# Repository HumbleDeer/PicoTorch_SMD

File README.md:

# PicoTorch

Forked from [kdb424]/[PicoTorch] under the [Fork Off Public License].

WIP heater and fan board. Specs will come later after a release version is finalized.
Fork is here to try and add SMD compatibility without compromising on the original design or THT parts.

[kdb424]: https://git.kdb424.xyz/kdb424
[PicoTorch]: https://git.kdb424.xyz/kdb424/PicoTorch 
[Fork Off Public License]: https://github.com/klardotsh/fork-off-public-license

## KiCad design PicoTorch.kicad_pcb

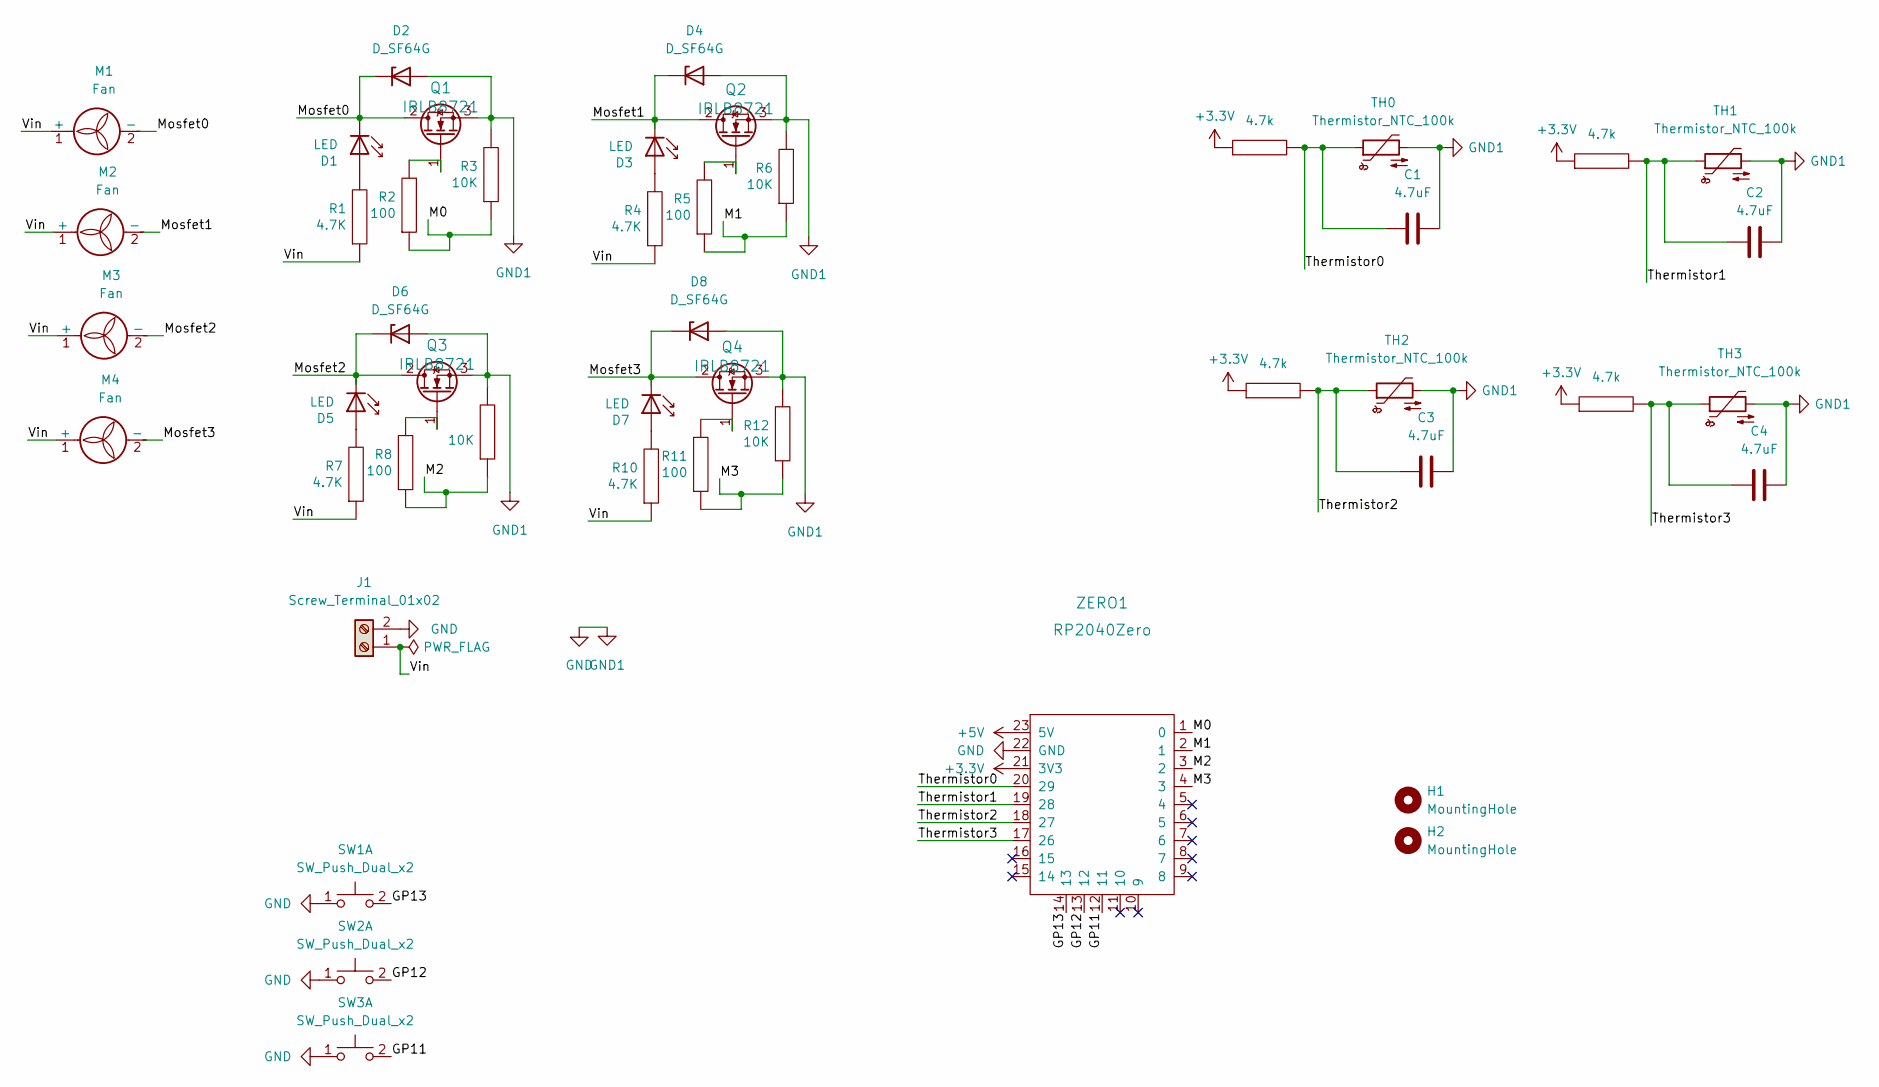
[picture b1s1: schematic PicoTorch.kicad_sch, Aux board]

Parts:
C1, C2, C3, C4: 4.7uF; CP_Radial_D4.0mm_P1.50mm
D1, D3, D5, D7: LED; LED_D1.8mm_W3.3mm_H2.4mm
D2, D4, D6, D8: D_SF64G; D_DO-34_SOD68_P7.62mm_Horizontal
H1, H2: MountingHole; MountingHole_3.2mm_M3_DIN965_Pad
J1: Screw_Terminal_01x02; TerminalBlock_Phoenix_MKDS-1,5-2_1x02_P5.00mm_Horizontal
M1, M2, M3: Fan; JST_XH_B2B-XH-A_1x02_P2.50mm_Vertical
M4: Fan; TerminalBlock_Phoenix_MKDS-1,5-2_1x02_P5.00mm_Horizontal
Q1, Q2, Q3, Q4: IRLB8721; TO-220-3_Horizontal_TabDown; MPN IRLML6344TRPBF; Digi-Key_PN IRLML6344TRPBFCT-ND
R1, R4, R7, R10: 4.7K; R_Axial_DIN0207_L6.3mm_D2.5mm_P2.54mm_Vertical; MPN RC0805JR-074K7L; LCSC C17673
R2, R5, R8, R11: 100; R_Axial_DIN0207_L6.3mm_D2.5mm_P2.54mm_Vertical; MPN RC0805JR-07100RL; LCSC C17408
R3, R6, R9, R12: 10K; R_Axial_DIN0207_L6.3mm_D2.5mm_P2.54mm_Vertical; MPN RC0805JR-0710KL; LCSC C17414
SW1, SW2, SW3: SW_Push_Dual_x2; JST_XH_B2B-XH-A_1x02_P2.50mm_Vertical
T1R1, T1R2, T1R3, T1R4: 4.7k; R_Axial_DIN0207_L6.3mm_D2.5mm_P2.54mm_Vertical
TH0, TH1, TH2, TH3: Thermistor_NTC_100k; JST_XH_B2B-XH-A_1x02_P2.50mm_Vertical
ZERO1: RP2040Zero; rp2040-zero-tht

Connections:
+3.3V: T1R1.1, T1R2.1, T1R3.1, T1R4.1, ZERO1.21 (3V3)
+5V: ZERO1.23 (5V)
/GP11: SW3.2 (D), ZERO1.12 (11)
/GP12: SW2.2 (D), ZERO1.13 (12)
/GP13: SW1.2 (D), ZERO1.14 (13)
/M0: R2.1, R3.1, ZERO1.1 (0)
/M1: R5.1, R6.1, ZERO1.2 (1)
/M2: R8.1, R9.1, ZERO1.3 (2)
/M3: R11.1, R12.1, ZERO1.4 (3)
/Mosfet0: D1.1 (K), D2.1 (K), M1.2 (-), Q1.2 (D)
/Mosfet1: D3.1 (K), D4.1 (K), M2.2 (-), Q2.2 (D)
/Mosfet2: D5.1 (K), D6.1 (K), M3.2 (-), Q3.2 (D)
/Mosfet3: D7.1 (K), D8.1 (K), M4.2 (-), Q4.2 (D)
/Thermistor0: C1.1, T1R1.2, TH0.1, ZERO1.20 (29)
/Thermistor1: C2.1, T1R2.2, TH1.1, ZERO1.19 (28)
/Thermistor2: C3.1, T1R3.2, TH2.1, ZERO1.18 (27)
/Thermistor3: C4.1, T1R4.2, TH3.1, ZERO1.17 (26)
/Vin: J1.1, M1.1 (+), M2.1 (+), M3.1 (+), M4.1 (+), R1.1, R4.1, R7.1, R10.1
GND: C1.2, C2.2, C3.2, C4.2, D2.2 (A), D4.2 (A), D6.2 (A), D8.2 (A), J1.2, Q1.3 (S), Q2.3 (S), Q3.3 (S), Q4.3 (S), R3.2, R6.2, R9.2, R12.2, SW1.1 (C), SW2.1 (C), SW3.1 (C), TH0.2, TH1.2, TH2.2, TH3.2, ZERO1.22 (GND)
unnamed: D1.2 (A), R1.2
unnamed: D3.2 (A), R4.2
unnamed: D5.2 (A), R7.2
unnamed: D7.2 (A), R10.2
unnamed: Q1.1 (G), R2.2
unnamed: Q2.1 (G), R5.2
unnamed: Q3.1 (G), R8.2
unnamed: Q4.1 (G), R11.2

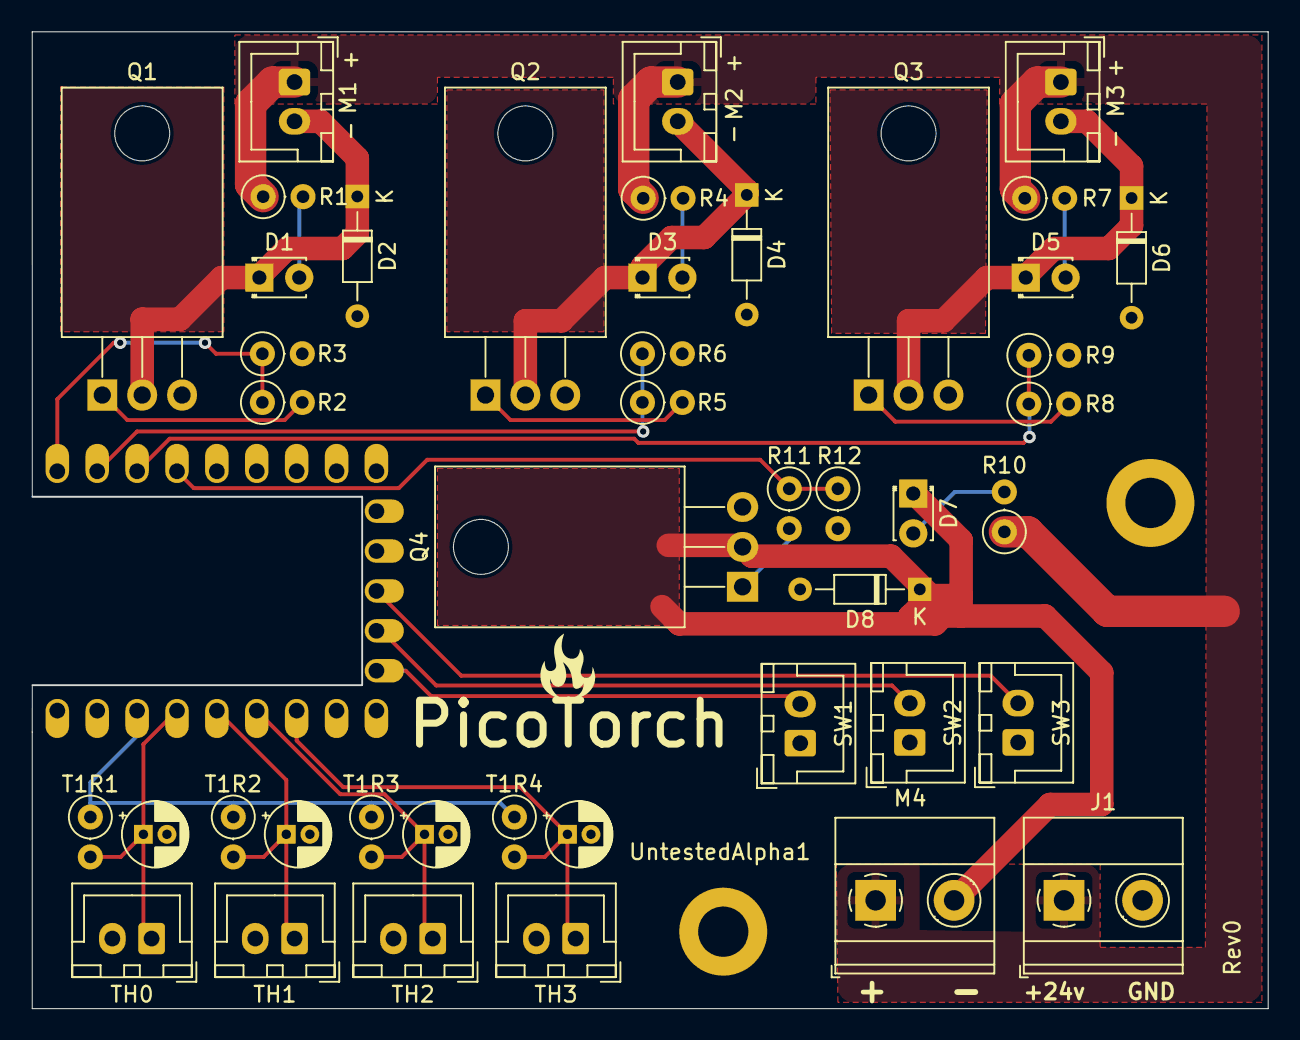
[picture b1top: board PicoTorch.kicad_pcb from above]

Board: 2 copper layers, 78.7 x 62.1 mm, 47 parts (0 on the bottom side), 26 nets.

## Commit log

2023-08-27 feat: First untested release
    This has not been tested. It passes ERC and DRC, but zero actual
    physical testing of this board has been done. It needs to be ordered
    and tested to completion, as well as documenting amp limits of the
    board. Please reach out if you have done any testing.
2023-10-29 Add fork info to readme
